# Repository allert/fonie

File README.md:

# 🎵 Fonie - RFID Spotify Player

ESP32 + Raspberry Pi + PN532 NFC reader = automated Spotify playback

## Hardware
- **ESP32 WROOM** - RFID polling via I2C
- **PN532** - NFC/RFID reader (I2C mode)
- **Raspberry Pi 4** - Flask web UI + Spotify integration

## Quick Start

### Fresh Pi Setup
```bash
git clone https://github.com/YOUR_USERNAME/fonie.git
cd fonie
chmod +x setup.sh
./setup.sh
```

### Manual Setup
1. Raspberry Pi OS 64-bit
2. `pip3 install -r requirements.txt`
3. Edit `.env` with Spotify credentials
4. `systemctl start fonie`
5. Visit `http://fonie.local`

## Files
- `app.py` - Flask backend
- `setup.sh` - Automated setup script
- `templates/index.html` - Web UI
- `esp32/esp.ino` - ESP32 firmware

## Configuration
1. Get Spotify API credentials from [developer.spotify.com](https://developer.spotify.com)
2. Set in `.env`:
```
   SPOTIFY_CLIENT_ID=...
   SPOTIFY_CLIENT_SECRET=...
```

## ESP32 JSON Protocol
```json
{"event":"TAG_ON","uid":"4F02FB46F6180"}
{"event":"TAG_OFF","uid":"4F02FB46F6180"}
```

## License
MIT

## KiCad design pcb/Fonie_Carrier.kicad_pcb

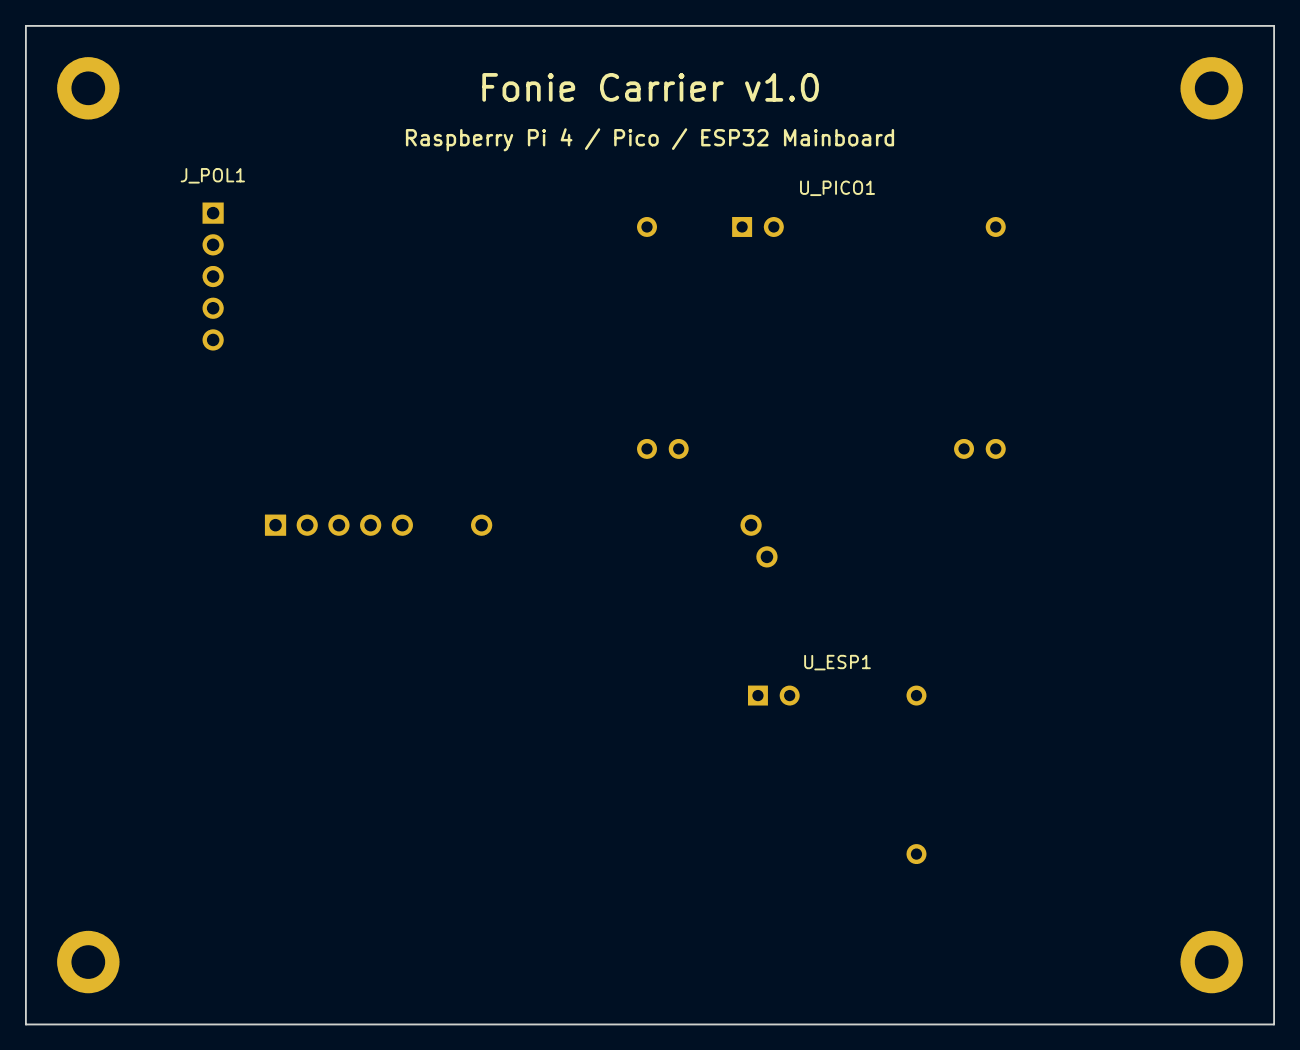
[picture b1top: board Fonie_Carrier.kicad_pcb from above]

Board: 2 copper layers, 100.0 x 80.0 mm, 4 parts (1 on the bottom side), 9 nets, no tracks yet.

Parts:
J_PI1: Pi4_GPIO; IDC-Header_2x20_P2.54mm_Vertical
J_POL1: Pololu2808; PinHeader_1x05_P2.54mm_Vertical
U_ESP1: ESP32-C3; ESP32-C3_SuperMini
U_PICO1: RP2040_Zero; Waveshare_RP2040_Zero

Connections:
+5V: J_PI1.2, J_PI1.4, J_POL1.3, U_ESP1.5V, U_PICO1.5V
GND: J_PI1.6, J_POL1.2, U_ESP1.GND, U_PICO1.GND
PI_ESP_RX: J_PI1.33, U_ESP1.21
PI_ESP_TX: J_PI1.32, U_ESP1.20
PI_PICO_RX: J_PI1.10, U_PICO1.0
PI_PICO_TX: J_PI1.8, U_PICO1.1
POLOLU_A: J_POL1.4, U_PICO1.26
POLOLU_OFF: J_POL1.5, U_PICO1.14
SHUTDOWN_SENSE: J_PI1.15, U_PICO1.8

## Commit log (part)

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2025-10-26 Initial commit: Fonie RFID player
2026-02-26 Commit before adding extra UART
2026-02-27 Last working version before big overhaul
2026-02-28 New yt-dlp version
2026-02-28 Added media to gitignore
2026-03-20 Working version before adding buttons
2026-05-16 Commit before crafting monorepo
2026-05-16 Monorepo restructuring and UART Ping/Pong mechanism
2026-05-16 Update deploy script path to ~/rfid-player
2026-05-16 Add captive portal and OTA logic
